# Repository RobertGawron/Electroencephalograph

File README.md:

# Electroencephalograph

**This project is unfinished.**

## Summary

Encephalograph is a noninvasive and relatively simple device to monitor brain activity. The device measure frequency of electric currents generated in various areas of brain. Those waves corresponds to activity of those brain areas.

This project is based on a single chip that integrates all EEG acquisition, this simplifies the design and reduce costs.

## System architecture

## Hardware

Hardware was done using KiCAD.

## Software

Software part is to be determinated.

# Hazards

* **Electrodes of the device are directly connected to human head, therefore high attention needs to be put on safety of the device.** The risk of electric shock was limited by using data/power isolation and inserting extra resistors and diode clamps in frontend of the device. **The device is a personal project and was not tested to any safety norms e.g. IEC 60601.**

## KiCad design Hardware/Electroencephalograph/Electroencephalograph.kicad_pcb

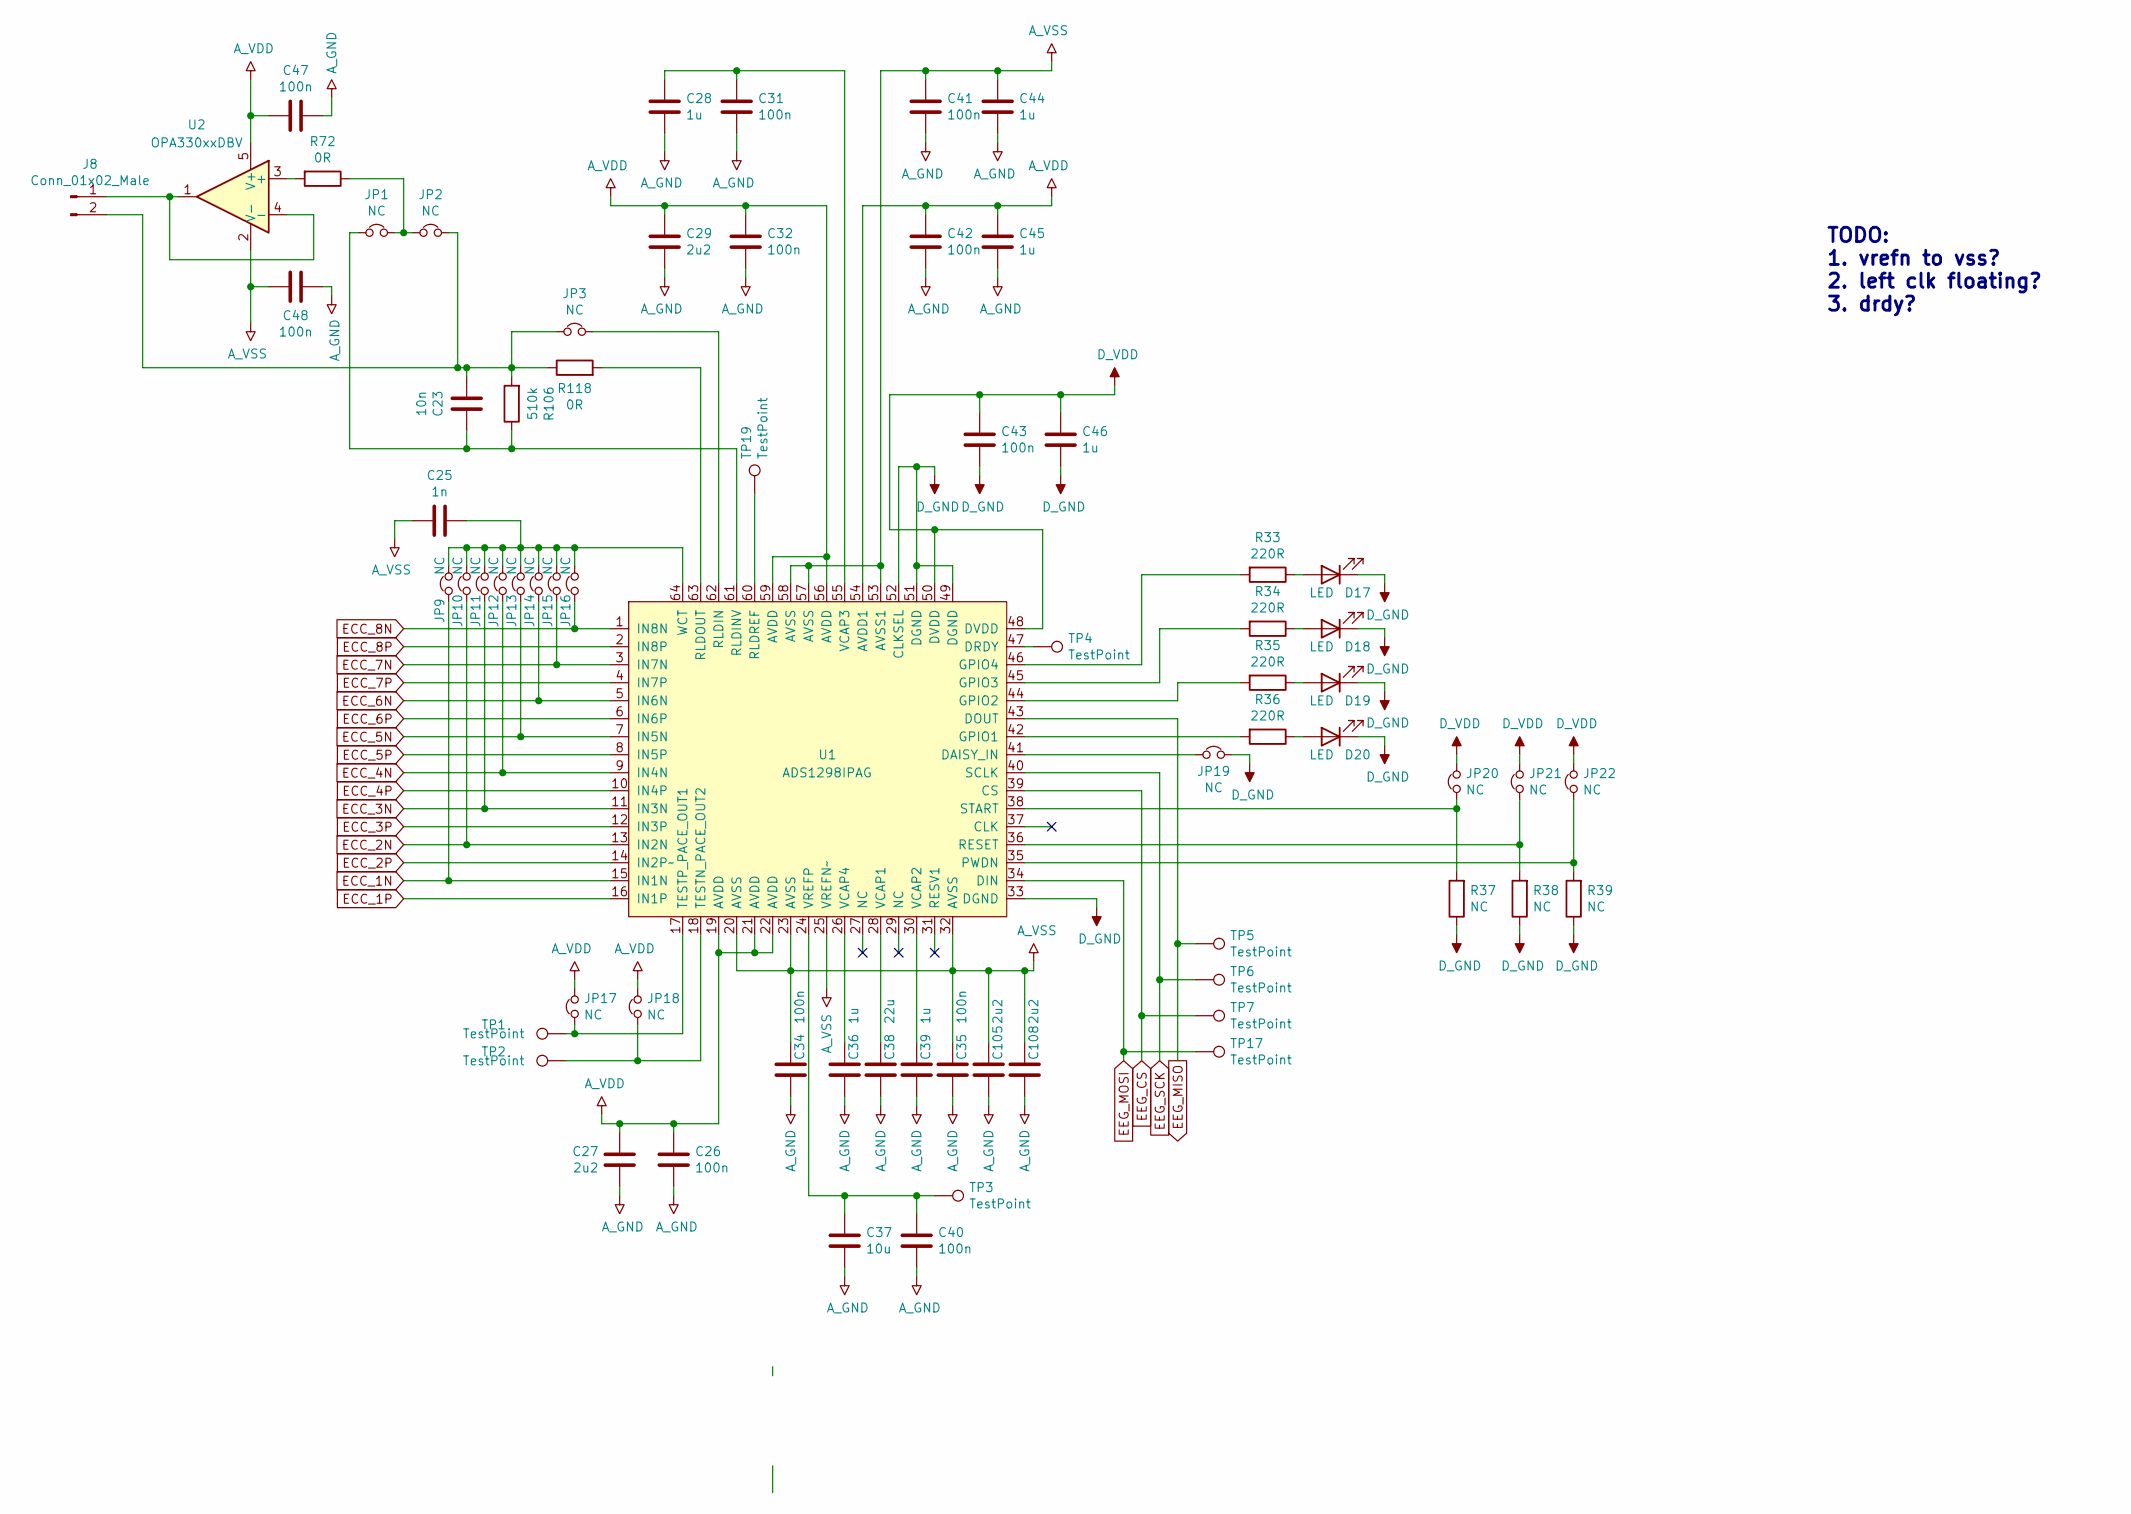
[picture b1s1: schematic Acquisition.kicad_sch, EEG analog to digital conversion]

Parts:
C23: 10n; C_0402_1005Metric
C25: 1n; C_0402_1005Metric
C26, C31, C32, C34, C35, C40, C41, C42, C43, C47, C48: 100n; C_0402_1005Metric
C27, C29, C105, C108: 2u2; C_0402_1005Metric
C28, C36, C39, C44, C45, C46: 1u; C_0402_1005Metric
C37: 10u; C_0805_2012Metric
C38: 22u; C_0805_2012Metric
D17, D18, D19, D20: LED; LED_0402_1005Metric
J8: Conn_01x02_Male; PinHeader_1x02_P2.54mm_Vertical
JP1, JP2, JP3, JP9, JP10, JP11, JP12, JP13, JP14, JP15, JP16, JP17, JP18, JP19, JP20, JP21, JP22: NC; SolderJumper-2_P1.3mm_Bridged_Pad1.0x1.5mm
R33, R34, R35, R36: 220R; R_0402_1005Metric
R37, R38, R39: NC; R_0402_1005Metric
R72, R118: 0R; R_0402_1005Metric
R106: 510k; R_0402_1005Metric
TP1, TP2, TP3, TP4, TP5, TP6, TP7, TP17, TP19: TestPoint; TestPoint_Pad_D1.0mm
U1: ADS1298IPAG; TQFP-64_10x10mm_P0.5mm
U2: OPA330xxDBV; SOT-23-5

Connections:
A_GND: C26.1, C27.2, C28.2, C29.1, C31.2, C32.1, C34.2, C35.2, C36.2, C37.2, C38.2, C39.2, C40.2, C41.1, C42.2, C44.1, C45.2, C47.2, C48.2, C105.2, C108.2; also elsewhere on the board
A_VDD: C26.2, C27.1, C29.2, C32.2, C42.1, C45.1, C47.1, JP17.1, JP18.1, U1.19 (AVDD), U1.21 (AVDD), U1.22 (AVDD), U1.54 (AVDD1), U1.56 (AVDD), U1.59 (AVDD), U2.5 (V+); also elsewhere on the board
A_VSS: C25.2, C34.1, C35.1, C41.2, C44.2, C48.1, C105.1, C108.1, U1.20 (AVSS), U1.23 (AVSS), U1.25 (VREFN~), U1.32 (AVSS), U1.53 (AVSS1), U1.57 (AVSS), U1.58 (AVSS), U2.2 (V-); also elsewhere on the board
D_GND: C43.2, C46.2, D17.1 (K), D18.1 (K), D19.1 (K), D20.1 (K), JP19.1, R37.1, R38.1, R39.1, U1.33 (DGND), U1.49 (DGND), U1.51 (DGND), U1.52 (CLKSEL); also elsewhere on the board
D_VDD: C43.1, C46.1, JP20.1, JP21.1, JP22.1, U1.48 (DVDD), U1.50 (DVDD); also elsewhere on the board
ECC_1N: JP9.2, U1.15 (IN1N); also elsewhere on the board
ECC_1P: U1.16 (IN1P); also elsewhere on the board
ECC_2N: JP10.2, U1.13 (IN2N); also elsewhere on the board
ECC_2P: U1.14 (IN2P~); also elsewhere on the board
ECC_3N: JP11.2, U1.11 (IN3N); also elsewhere on the board
ECC_3P: U1.12 (IN3P); also elsewhere on the board
ECC_4N: JP12.2, U1.9 (IN4N); also elsewhere on the board
ECC_4P: U1.10 (IN4P); also elsewhere on the board
ECC_5N: JP13.2, U1.7 (IN5N); also elsewhere on the board
ECC_5P: U1.8 (IN5P); also elsewhere on the board
ECC_6N: JP14.2, U1.5 (IN6N); also elsewhere on the board
ECC_6P: U1.6 (IN6P); also elsewhere on the board
ECC_7N: JP15.2, U1.3 (IN7N); also elsewhere on the board
ECC_7P: U1.4 (IN7P); also elsewhere on the board
ECC_8N: JP16.2, U1.1 (IN8N); also elsewhere on the board
ECC_8P: U1.2 (IN8P); also elsewhere on the board
EEG_CS: TP7.1, U1.39 (CS); also elsewhere on the board
EEG_MISO: TP5.1, U1.43 (DOUT); also elsewhere on the board
EEG_MOSI: TP17.1, U1.34 (DIN); also elsewhere on the board
EEG_SCK: TP6.1, U1.40 (SCLK); also elsewhere on the board
unnamed: C23.1, J8.2, JP2.1, JP3.2, R106.2, R118.1
unnamed: C23.2, JP1.2, R106.1, U1.61 (RLDINV)
unnamed: C25.1, JP9.1, JP10.1, JP11.1, JP12.1, JP13.1, JP14.1, JP15.1, JP16.1, U1.64 (WCT)
unnamed: C28.1, C31.1, U1.55 (VCAP3)
unnamed: C36.1, U1.26 (VCAP4)
unnamed: C37.1, C40.1, TP3.1, U1.24 (VREFP)
unnamed: C38.1, U1.28 (VCAP1)
unnamed: C39.1, U1.30 (VCAP2)
unnamed: D17.2 (A), R33.1
unnamed: D18.2 (A), R34.1
unnamed: D19.2 (A), R35.1
unnamed: D20.2 (A), R36.1
unnamed: J8.1, U2.1, U2.4 (-)
unnamed: JP1.1, JP2.2, R72.1
unnamed: JP3.1, U1.62 (RLDIN)
unnamed: JP17.2, TP1.1, U1.17 (TESTP_PACE_OUT1)
unnamed: JP18.2, TP2.1, U1.18 (TESTN_PACE_OUT2)
unnamed: JP19.2, U1.41 (DAISY_IN)
unnamed: JP20.2, R37.2, U1.38 (START)
unnamed: JP21.2, R38.2, U1.36 (RESET)
unnamed: JP22.2, R39.2, U1.35 (PWDN)
unnamed: R33.2, U1.46 (GPIO4)
unnamed: R34.2, U1.45 (GPIO3)
unnamed: R35.2, U1.44 (GPIO2)
unnamed: R36.2, U1.42 (GPIO1)
unnamed: R72.2, U2.3 (+)
unnamed: R118.2, U1.63 (RLDOUT)
unnamed: TP4.1, U1.47 (DRDY)
unnamed: TP19.1, U1.60 (RLDREF)

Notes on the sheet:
TODO: 1. vrefn to vss? 2. left clk floating? 3. drdy?

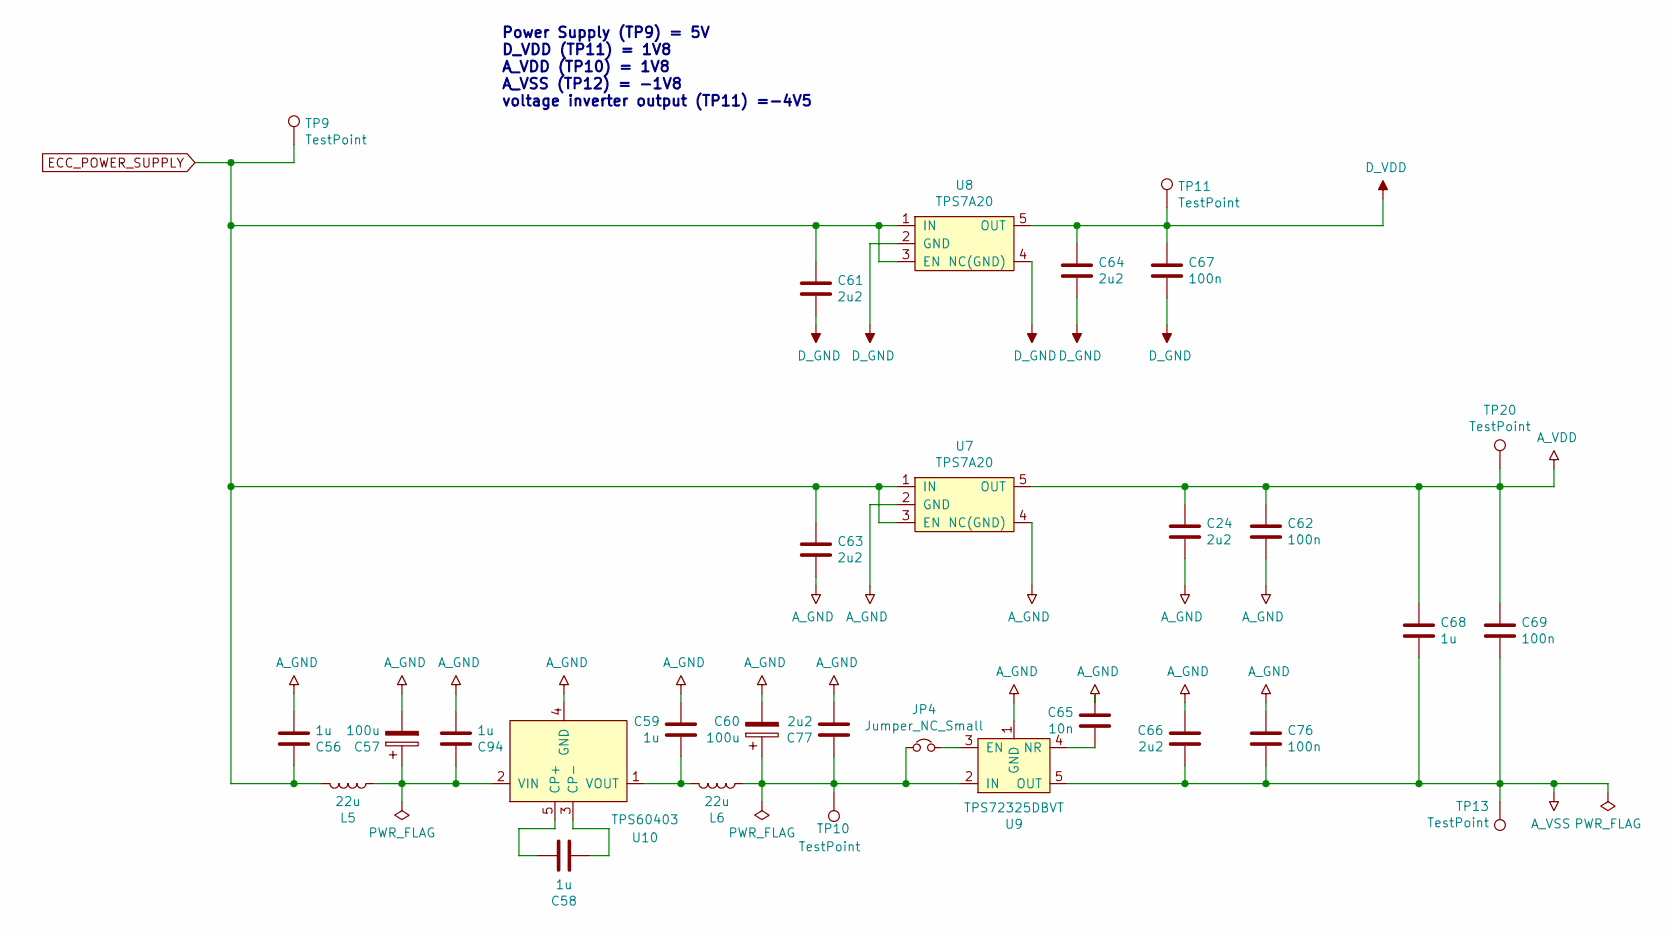
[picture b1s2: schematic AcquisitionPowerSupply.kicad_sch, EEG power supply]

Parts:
C24, C61, C63, C64, C66, C77: 2u2; C_0402_1005Metric
C56, C58, C59, C68, C94: 1u; C_0402_1005Metric
C57, C60: 100u; CP_Elec_6.3x5.8
C62, C67, C69, C76: 100n; C_0402_1005Metric
C65: 10n; C_0402_1005Metric
JP4: Jumper_NC_Small; SolderJumper-2_P1.3mm_Bridged_Pad1.0x1.5mm
L5, L6: 22u; L_7.3x7.3_H3.5
TP9, TP10, TP11, TP13, TP20: TestPoint; TestPoint_Pad_D1.0mm
U7, U8: TPS7A20; SOT-23-5
U9: TPS72325DBVT; SOT-23-5
U10: TPS60403; SOT-23-5

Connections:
A_GND: C24.2, C56.2, C57.2, C59.2, C60.2, C62.2, C63.2, C65.2, C66.2, C76.2, C77.2, C94.2, U7.2 (GND), U7.4 (NC(GND)), U9.1 (GND), U10.4 (GND); also elsewhere on the board
A_VDD: C24.1, C62.1, C68.1, C69.1, TP20.1, U7.5 (OUT); also elsewhere on the board
A_VSS: C66.1, C68.2, C69.2, C76.1, TP13.1, U9.5 (OUT); also elsewhere on the board
D_GND: C61.2, C64.2, C67.2, U8.2 (GND), U8.4 (NC(GND)); also elsewhere on the board
D_VDD: C64.1, C67.1, TP11.1, U8.5 (OUT); also elsewhere on the board
ECC_POWER_SUPPLY: C56.1, C61.1, C63.1, L5.2, TP9.1, U7.1 (IN), U7.3 (EN), U8.1 (IN), U8.3 (EN); also elsewhere on the board
unnamed: C57.1, C94.1, L5.1, U10.2 (VIN)
unnamed: C58.1, U10.3 (CP-)
unnamed: C58.2, U10.5 (CP+)
unnamed: C59.1, L6.2, U10.1 (VOUT)
unnamed: C60.1, C77.1, JP4.1, L6.1, TP10.1, U9.2 (IN)
unnamed: C65.1, U9.4 (NR)
unnamed: JP4.2, U9.3 (EN)

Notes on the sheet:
Power Supply (TP9) = 5V D_VDD (TP11) = 1V8 A_VDD (TP10) = 1V8 A_VSS (TP12) = -1V8 voltage inverter output (TP11) =-4V5

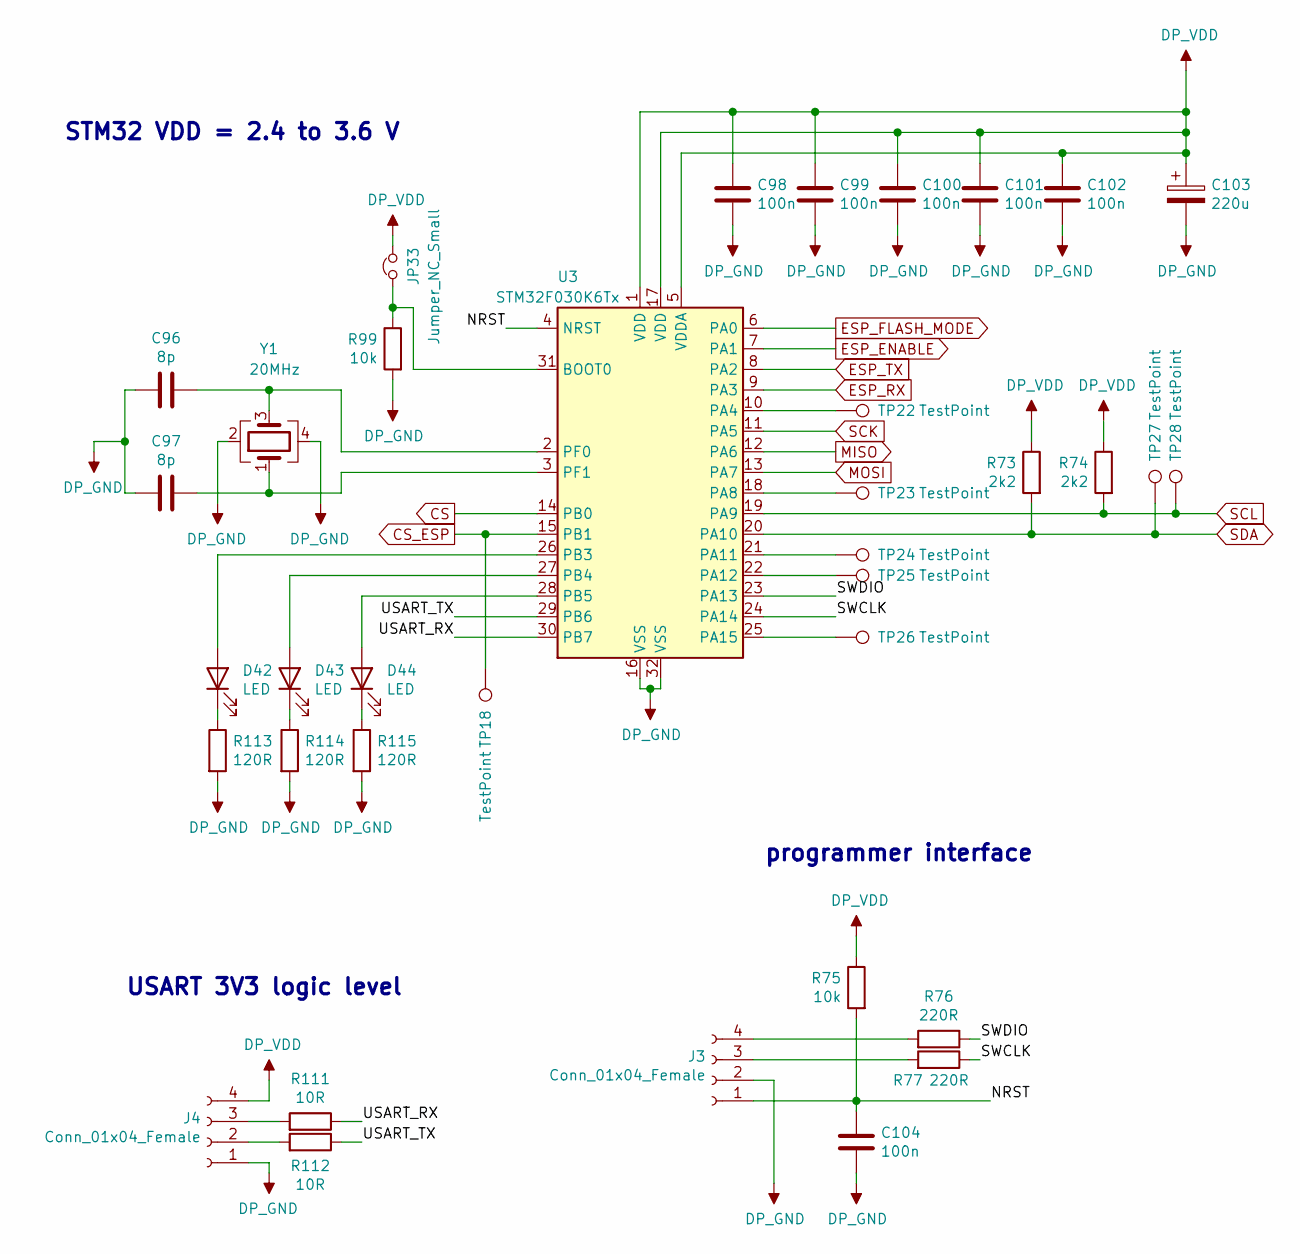
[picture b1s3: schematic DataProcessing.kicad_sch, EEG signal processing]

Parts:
C96, C97: 8p; C_0402_1005Metric
C98, C99, C100, C101, C102, C104: 100n; C_0402_1005Metric
C103: 220u; CP_Elec_6.3x5.8
D42, D43, D44: LED; LED_0402_1005Metric
J3, J4: Conn_01x04_Female; PinHeader_1x04_P2.54mm_Vertical
JP33: Jumper_NC_Small; SolderJumper-2_P1.3mm_Bridged2Bar_RoundedPad1.0x1.5mm
R73, R74: 2k2; R_0402_1005Metric
R75, R99: 10k; R_0402_1005Metric
R76, R77: 220R; R_0402_1005Metric
R111, R112: 10R; R_0402_1005Metric
R113, R114, R115: 120R; R_0402_1005Metric
TP18, TP22, TP23, TP24, TP25, TP26, TP27, TP28: TestPoint; TestPoint_Pad_D1.0mm
U3: STM32F030K6Tx; LQFP-32_7x7mm_P0.8mm
Y1: 20MHz; Oscillator_SMD_EuroQuartz_XO53-4Pin_5.0x3.2mm

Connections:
/DataProcessing/NRST: C104.1, J3.1, R75.2, U3.4 (NRST)
/DataProcessing/SWCLK: R77.1, U3.24 (PA14)
/DataProcessing/SWDIO: R76.1, U3.23 (PA13)
/DataProcessing/USART_RX: R111.1, U3.30 (PB7)
/DataProcessing/USART_TX: R112.1, U3.29 (PB6)
CS: U3.14 (PB0); also elsewhere on the board
CS_ESP: TP18.1, U3.15 (PB1); also elsewhere on the board
DP_GND: C96.1, C97.1, C98.2, C99.2, C100.2, C101.2, C102.2, C103.2, C104.2, J3.2, J4.1, R99.2, R113.2, R114.2, R115.2, U3.16 (VSS), U3.32 (VSS), Y1.2, Y1.4; also elsewhere on the board
DP_VDD: C98.1, C99.1, C100.1, C101.1, C102.1, C103.1, J4.4, JP33.1, R73.1, R74.1, R75.1, U3.1 (VDD), U3.5 (VDDA), U3.17 (VDD); also elsewhere on the board
ESP_ENABLE: U3.7 (PA1); also elsewhere on the board
ESP_FLASH_MODE: U3.6 (PA0); also elsewhere on the board
ESP_RX: U3.9 (PA3); also elsewhere on the board
ESP_TX: U3.8 (PA2); also elsewhere on the board
MISO: U3.12 (PA6); also elsewhere on the board
MOSI: U3.13 (PA7); also elsewhere on the board
unnamed: C96.2, U3.2 (PF0), Y1.3
unnamed: C97.2, U3.3 (PF1), Y1.1
unnamed: D42.1 (K), R113.1
unnamed: D42.2 (A), U3.26 (PB3)
unnamed: D43.1 (K), R114.1
unnamed: D43.2 (A), U3.27 (PB4)
unnamed: D44.1 (K), R115.1
unnamed: D44.2 (A), U3.28 (PB5)
unnamed: J3.3, R77.2
unnamed: J3.4, R76.2
unnamed: J4.2, R112.2
unnamed: J4.3, R111.2
unnamed: JP33.2, R99.1, U3.31 (BOOT0)
unnamed: TP22.1, U3.10 (PA4)
unnamed: TP23.1, U3.18 (PA8)
unnamed: TP24.1, U3.21 (PA11)
unnamed: TP25.1, U3.22 (PA12)
unnamed: TP26.1, U3.25 (PA15)
SCK: U3.11 (PA5); also elsewhere on the board
SCL: R74.2, TP28.1, U3.19 (PA9); also elsewhere on the board
SDA: R73.2, TP27.1, U3.20 (PA10); also elsewhere on the board

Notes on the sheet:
STM32 VDD = 2.4 to 3.6 V
USART 3V3 logic level
programmer interface

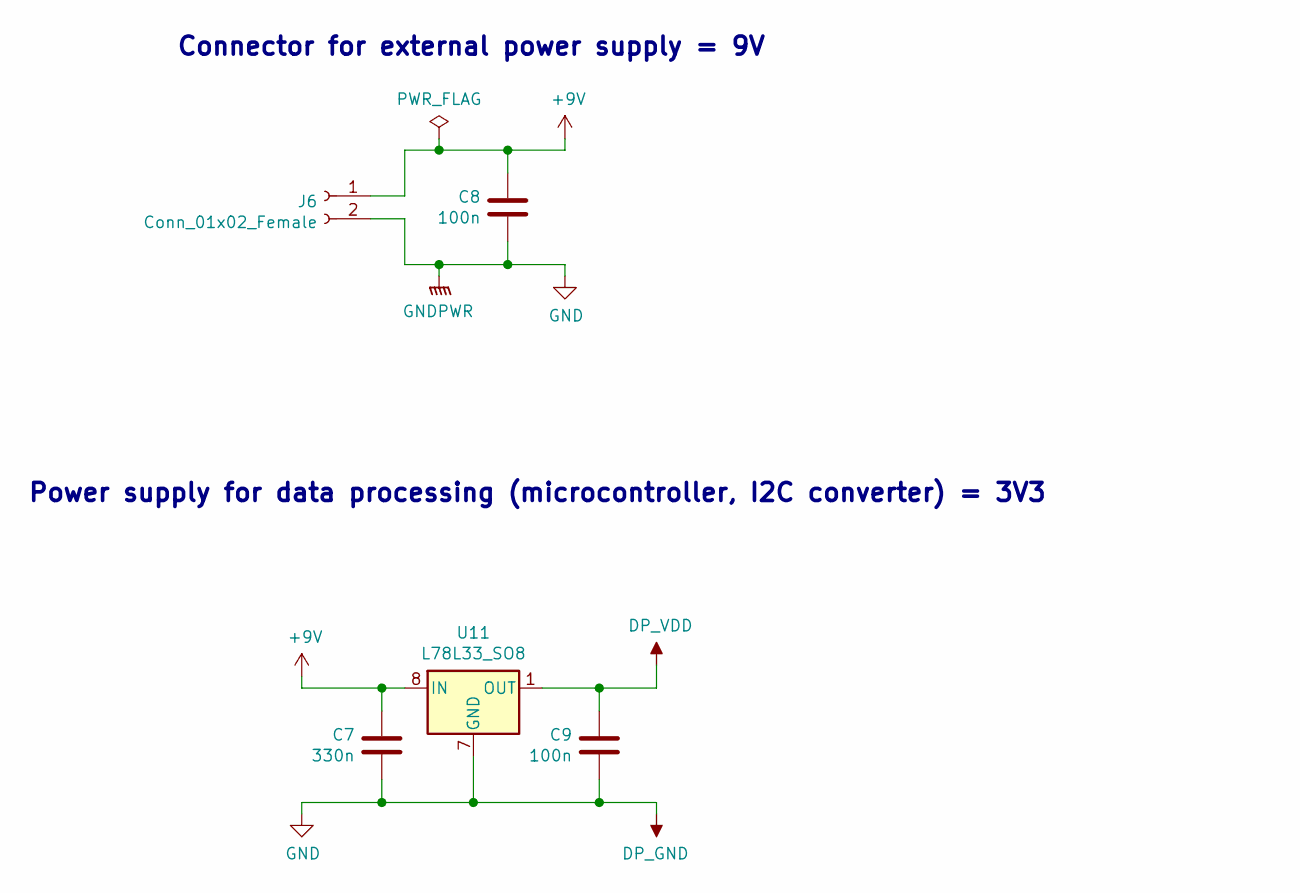
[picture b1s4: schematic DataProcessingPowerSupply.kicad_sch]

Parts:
C7: 330n; C_0402_1005Metric
C8, C9: 100n; C_0402_1005Metric
J6: Conn_01x02_Female; PinHeader_1x02_P2.54mm_Vertical
U11: L78L33_SO8; SOIC-8_3.9x4.9mm_P1.27mm

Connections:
+9V: C7.1, C8.1, J6.1, U11.8 (IN)
DP_GND: C7.2, C8.2, C9.2, J6.2, U11.2 (GND), U11.3 (GND), U11.6 (GND), U11.7 (GND); also elsewhere on the board
DP_VDD: C9.1, U11.1 (OUT); also elsewhere on the board

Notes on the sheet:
Power supply for data processing (microcontroller, I2C converter) = 3V3
Connector for external power supply = 9V

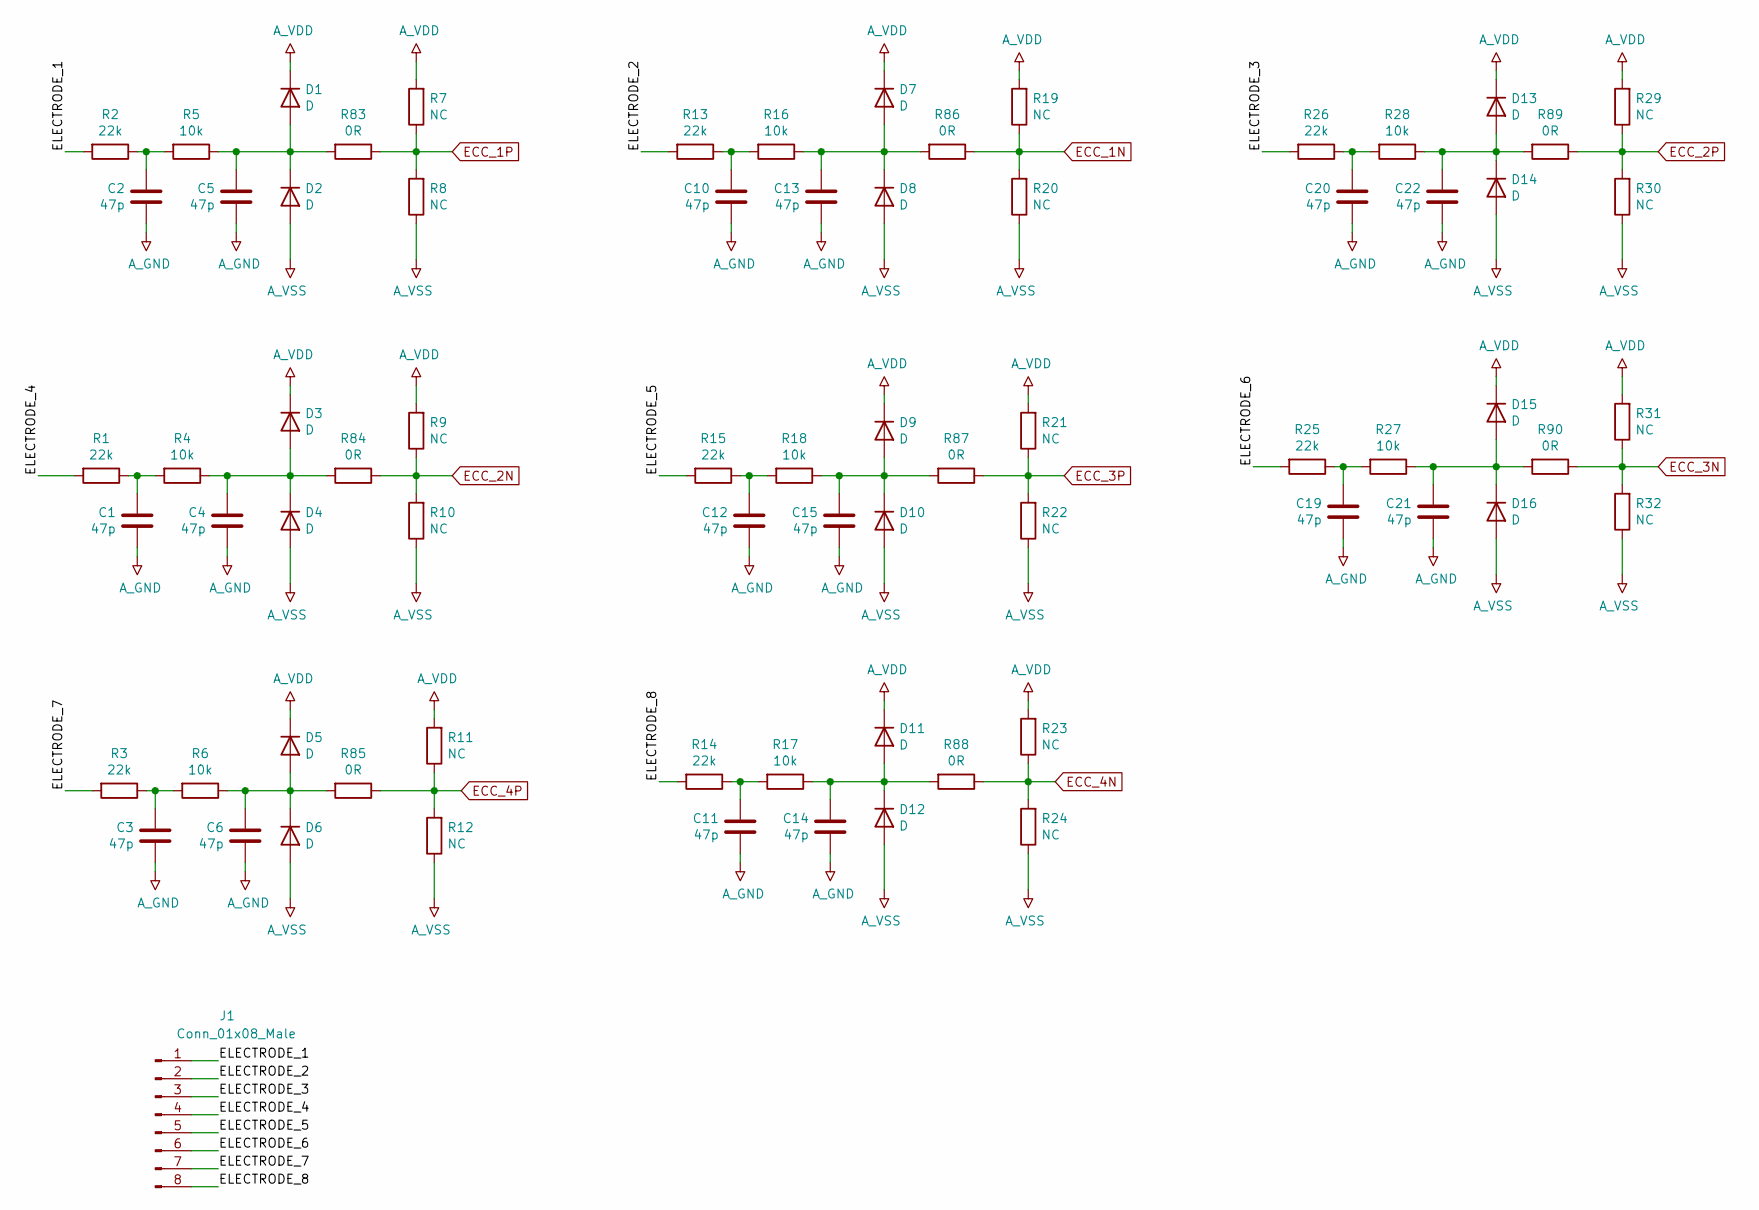
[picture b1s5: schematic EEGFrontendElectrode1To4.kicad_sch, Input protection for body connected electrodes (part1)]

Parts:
C1, C2, C3, C4, C5, C6, C10, C11, C12, C13, C14, C15, C19, C20, C21, C22: 47p; C_0402_1005Metric
D1, D2, D3, D4, D5, D6, D7, D8, D9, D10, D11, D12, D13, D14, D15, D16: D; D_MELF
J1: Conn_01x08_Male; PinHeader_1x08_P2.54mm_Horizontal
R1, R2, R3, R13, R14, R15, R25, R26: 22k; R_MELF_MMB-0207
R4, R5, R6, R16, R17, R18, R27, R28: 10k; R_MELF_MMB-0207
R7, R8, R9, R10, R11, R12, R19, R20, R21, R22, R23, R24, R29, R30, R31, R32: NC; R_0402_1005Metric
R83, R84, R85, R86, R87, R88, R89, R90: 0R; R_0402_1005Metric

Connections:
/EEGFrontendElectrode1To4/ELECTRODE_1: J1.1, R2.2
/EEGFrontendElectrode1To4/ELECTRODE_2: J1.2, R13.2
/EEGFrontendElectrode1To4/ELECTRODE_3: J1.3, R26.2
/EEGFrontendElectrode1To4/ELECTRODE_4: J1.4, R1.2
/EEGFrontendElectrode1To4/ELECTRODE_5: J1.5, R15.2
/EEGFrontendElectrode1To4/ELECTRODE_6: J1.6, R25.2
/EEGFrontendElectrode1To4/ELECTRODE_7: J1.7, R3.2
/EEGFrontendElectrode1To4/ELECTRODE_8: J1.8, R14.2
A_GND: C1.2, C2.2, C3.2, C4.2, C5.2, C6.2, C10.2, C11.2, C12.2, C13.2, C14.2, C15.2, C19.2, C20.2, C21.2, C22.2; also elsewhere on the board
A_VDD: D1.1 (K), D3.1 (K), D5.1 (K), D7.1 (K), D9.1 (K), D11.1 (K), D13.1 (K), D15.1 (K), R7.2, R9.2, R11.2, R19.2, R21.2, R23.2, R29.2, R31.2; also elsewhere on the board
A_VSS: D2.2 (A), D4.2 (A), D6.2 (A), D8.2 (A), D10.2 (A), D12.2 (A), D14.2 (A), D16.2 (A), R8.1, R10.1, R12.1, R20.1, R22.1, R24.1, R30.1, R32.1; also elsewhere on the board
ECC_1N: R19.1, R20.2, R86.1; also elsewhere on the board
ECC_1P: R7.1, R8.2, R83.1; also elsewhere on the board
ECC_2N: R9.1, R10.2, R84.1; also elsewhere on the board
ECC_2P: R29.1, R30.2, R89.1; also elsewhere on the board
ECC_3N: R31.1, R32.2, R90.1; also elsewhere on the board
ECC_3P: R21.1, R22.2, R87.1; also elsewhere on the board
ECC_4N: R23.1, R24.2, R88.1; also elsewhere on the board
ECC_4P: R11.1, R12.2, R85.1; also elsewhere on the board
unnamed: C1.1, R1.1, R4.2
unnamed: C2.1, R2.1, R5.2
unnamed: C3.1, R3.1, R6.2
unnamed: C4.1, D3.2 (A), D4.1 (K), R4.1, R84.2
unnamed: C5.1, D1.2 (A), D2.1 (K), R5.1, R83.2
unnamed: C6.1, D5.2 (A), D6.1 (K), R6.1, R85.2
unnamed: C10.1, R13.1, R16.2
unnamed: C11.1, R14.1, R17.2
unnamed: C12.1, R15.1, R18.2
unnamed: C13.1, D7.2 (A), D8.1 (K), R16.1, R86.2
unnamed: C14.1, D11.2 (A), D12.1 (K), R17.1, R88.2
unnamed: C15.1, D9.2 (A), D10.1 (K), R18.1, R87.2
unnamed: C19.1, R25.1, R27.2
unnamed: C20.1, R26.1, R28.2
unnamed: C21.1, D15.2 (A), D16.1 (K), R27.1, R90.2
unnamed: C22.1, D13.2 (A), D14.1 (K), R28.1, R89.2

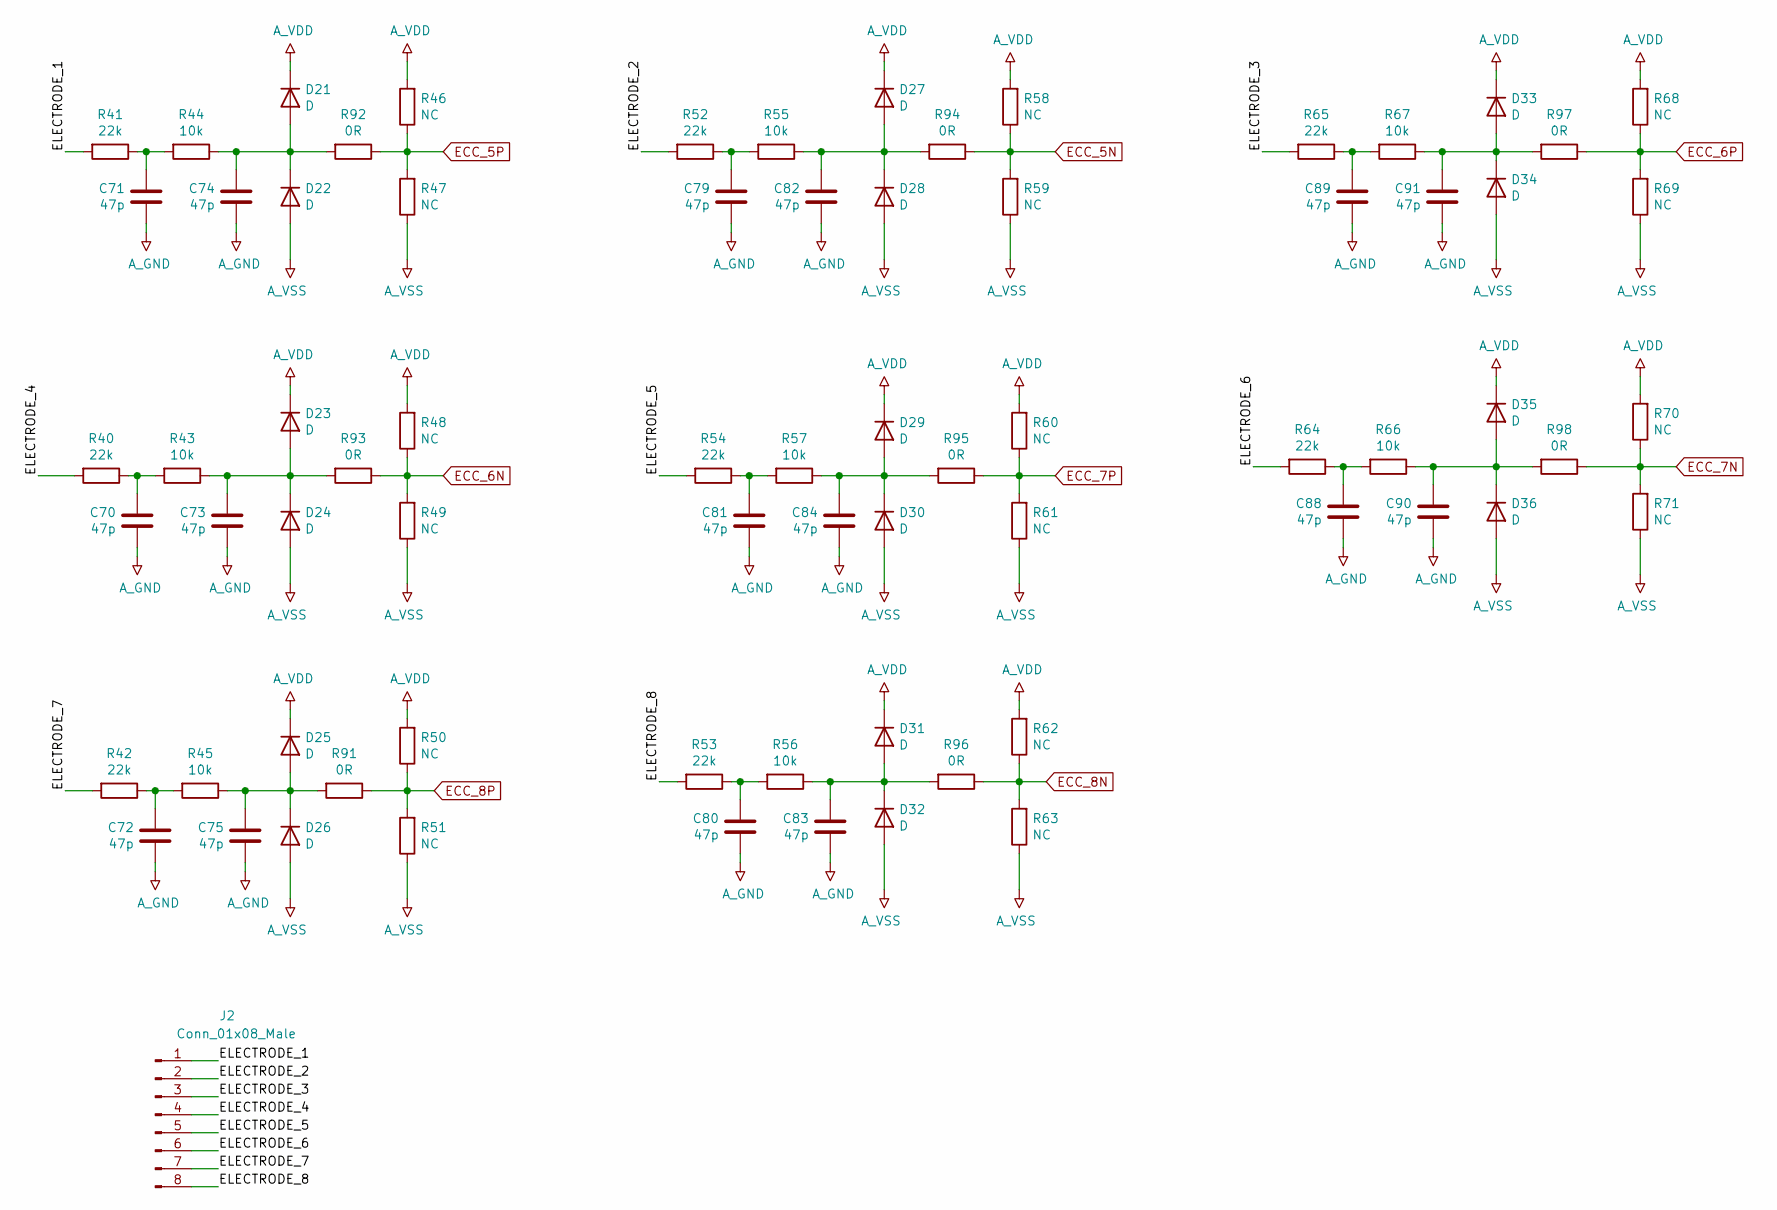
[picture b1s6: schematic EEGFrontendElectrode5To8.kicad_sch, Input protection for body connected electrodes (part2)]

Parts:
C70, C71, C72, C73, C74, C75, C79, C80, C81, C82, C83, C84, C88, C89, C90, C91: 47p; C_0402_1005Metric
D21, D22, D23, D24, D25, D26, D27, D28, D29, D30, D31, D32, D33, D34, D35, D36: D; D_MELF
J2: Conn_01x08_Male; PinHeader_1x08_P2.54mm_Horizontal
R40, R41, R42, R52, R53, R54, R64, R65: 22k; R_MELF_MMB-0207
R43, R44, R45, R55, R56, R57, R66, R67: 10k; R_MELF_MMB-0207
R46, R47, R48, R49, R50, R51, R58, R59, R60, R61, R62, R63, R68, R69, R70, R71: NC; R_0402_1005Metric
R91, R92, R93, R94, R95, R96, R97, R98: 0R; R_0402_1005Metric

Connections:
/EEGFrontendElectrode5To8/ELECTRODE_1: J2.1, R41.2
/EEGFrontendElectrode5To8/ELECTRODE_2: J2.2, R52.2
/EEGFrontendElectrode5To8/ELECTRODE_3: J2.3, R65.2
/EEGFrontendElectrode5To8/ELECTRODE_4: J2.4, R40.2
/EEGFrontendElectrode5To8/ELECTRODE_5: J2.5, R54.2
/EEGFrontendElectrode5To8/ELECTRODE_6: J2.6, R64.2
/EEGFrontendElectrode5To8/ELECTRODE_7: J2.7, R42.2
/EEGFrontendElectrode5To8/ELECTRODE_8: J2.8, R53.2
A_GND: C70.2, C71.2, C72.2, C73.2, C74.2, C75.2, C79.2, C80.2, C81.2, C82.2, C83.2, C84.2, C88.2, C89.2, C90.2, C91.2; also elsewhere on the board
A_VDD: D21.1 (K), D23.1 (K), D25.1 (K), D27.1 (K), D29.1 (K), D31.1 (K), D33.1 (K), D35.1 (K), R46.2, R48.2, R50.2, R58.2, R60.2, R62.2, R68.2, R70.2; also elsewhere on the board
A_VSS: D22.2 (A), D24.2 (A), D26.2 (A), D28.2 (A), D30.2 (A), D32.2 (A), D34.2 (A), D36.2 (A), R47.1, R49.1, R51.1, R59.1, R61.1, R63.1, R69.1, R71.1; also elsewhere on the board
ECC_5N: R58.1, R59.2, R94.1; also elsewhere on the board
ECC_5P: R46.1, R47.2, R92.1; also elsewhere on the board
ECC_6N: R48.1, R49.2, R93.1; also elsewhere on the board
ECC_6P: R68.1, R69.2, R97.1; also elsewhere on the board
ECC_7N: R70.1, R71.2, R98.1; also elsewhere on the board
ECC_7P: R60.1, R61.2, R95.1; also elsewhere on the board
ECC_8N: R62.1, R63.2, R96.1; also elsewhere on the board
ECC_8P: R50.1, R51.2, R91.1; also elsewhere on the board
unnamed: C70.1, R40.1, R43.2
unnamed: C71.1, R41.1, R44.2
unnamed: C72.1, R42.1, R45.2
unnamed: C73.1, D23.2 (A), D24.1 (K), R43.1, R93.2
unnamed: C74.1, D21.2 (A), D22.1 (K), R44.1, R92.2
unnamed: C75.1, D25.2 (A), D26.1 (K), R45.1, R91.2
unnamed: C79.1, R52.1, R55.2
unnamed: C80.1, R53.1, R56.2
unnamed: C81.1, R54.1, R57.2
unnamed: C82.1, D27.2 (A), D28.1 (K), R55.1, R94.2
unnamed: C83.1, D31.2 (A), D32.1 (K), R56.1, R96.2
unnamed: C84.1, D29.2 (A), D30.1 (K), R57.1, R95.2
unnamed: C88.1, R64.1, R66.2
unnamed: C89.1, R65.1, R67.2
unnamed: C90.1, D35.2 (A), D36.1 (K), R66.1, R98.2
unnamed: C91.1, D33.2 (A), D34.1 (K), R67.1, R97.2

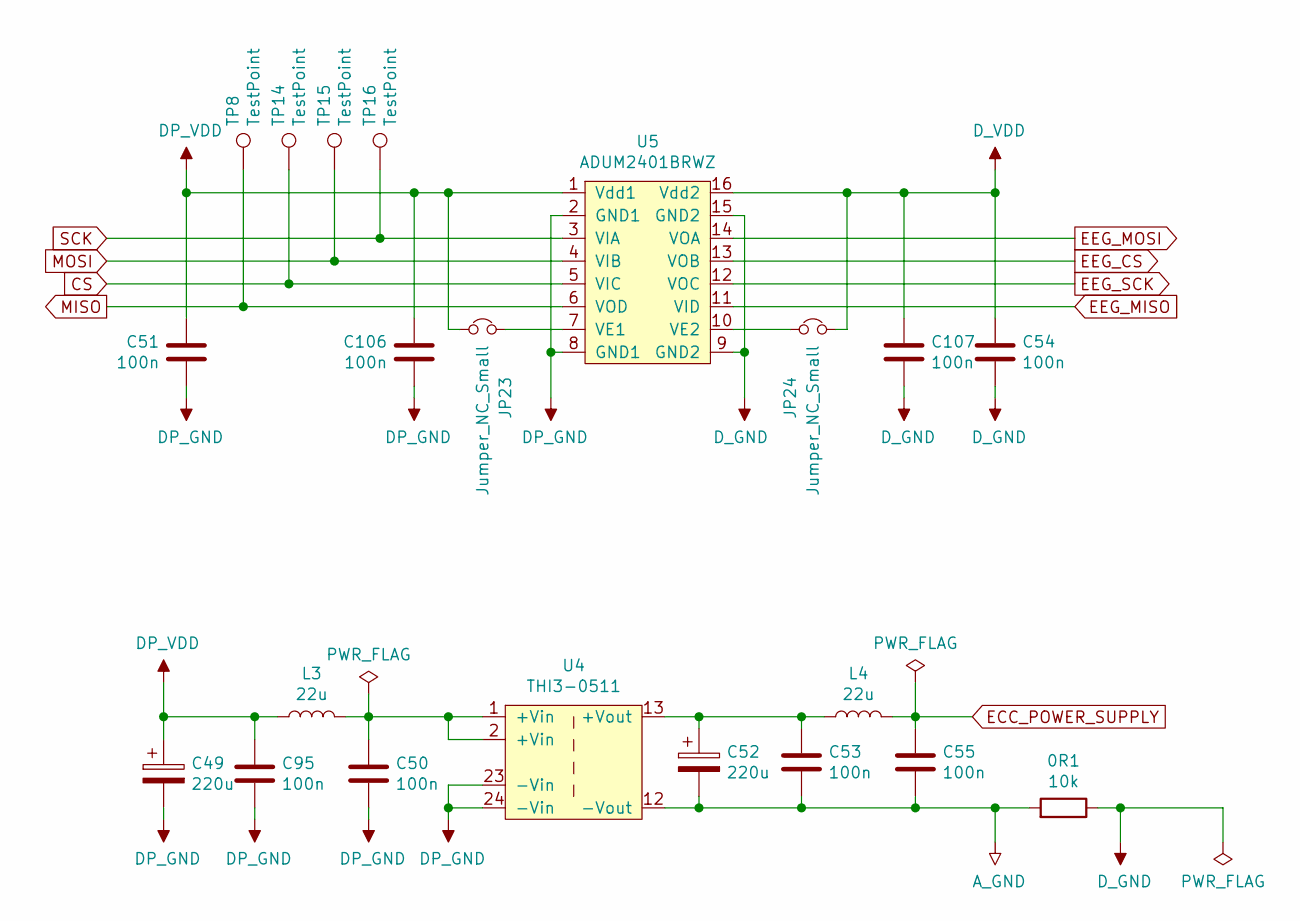
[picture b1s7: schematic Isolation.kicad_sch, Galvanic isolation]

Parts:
0R1: 10k; R_0402_1005Metric
C49, C52: 220u; CP_Elec_6.3x5.8
C50, C51, C53, C54, C55, C95, C106, C107: 100n; C_0402_1005Metric
JP23, JP24: Jumper_NC_Small; SolderJumper-2_P1.3mm_Bridged_Pad1.0x1.5mm
L3, L4: 22u; L_7.3x7.3_H3.5
TP8, TP14, TP15, TP16: TestPoint; TestPoint_Pad_D1.0mm
U4: THI3-0511
U5: ADUM2401BRWZ; SOIC-16W_7.5x10.3mm_P1.27mm

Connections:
A_GND: 0R1.2, C52.2, C53.2, C55.2, U4.12 (-Vout); also elsewhere on the board
CS: TP14.1, U5.5 (VIC); also elsewhere on the board
DP_GND: C49.2, C50.2, C51.2, C95.2, C106.2, U4.23 (-Vin), U4.24 (-Vin), U5.2 (GND1), U5.8 (GND1); also elsewhere on the board
DP_VDD: C49.1, C51.1, C95.1, C106.1, JP23.2, L3.1, U5.1 (Vdd1); also elsewhere on the board
D_GND: 0R1.1, C54.2, C107.2, U5.9 (GND2), U5.15 (GND2); also elsewhere on the board
D_VDD: C54.1, C107.1, JP24.2, U5.16 (Vdd2); also elsewhere on the board
ECC_POWER_SUPPLY: C55.1, L4.2; also elsewhere on the board
EEG_CS: U5.13 (VOB); also elsewhere on the board
EEG_MISO: U5.11 (VID); also elsewhere on the board
EEG_MOSI: U5.14 (VOA); also elsewhere on the board
EEG_SCK: U5.12 (VOC); also elsewhere on the board
MISO: TP8.1, U5.6 (VOD); also elsewhere on the board
MOSI: TP15.1, U5.4 (VIB); also elsewhere on the board
unnamed: C50.1, L3.2, U4.1 (+Vin), U4.2 (+Vin)
unnamed: C52.1, C53.1, L4.1, U4.13 (+Vout)
unnamed: JP23.1, U5.7 (VE1)
unnamed: JP24.1, U5.10 (VE2)
SCK: TP16.1, U5.3 (VIA); also elsewhere on the board

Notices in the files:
Hardware/Electroencephalograph/Acquisition.kicad_sch:
MIT License
